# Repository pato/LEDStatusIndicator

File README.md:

LEDStatusIndicator
==================

Handy device that you can use to inform people outside your dorm on whether you are available, working, sleeping, or in need of solitude

First Protype
-------------
The first prototype was just a breadboard with four LEDs. There was no way of changing color besides manually using a jump cable to power them.

Second Protype
--------------
The second prototype did not use a breadboard, instead I soldered the cables to the resistors to the LEDs. The anodes are all soldered together and the cathod so the LEDs are toggled by manually providing power to the desired LED.

Third Prototype
---------------
The third prototype was housed in a cardboard box, the cables to power the LEDs would go over and around the door to the inside of the room where I could control which lights turn on.

Fourth Prototype
----------------
The fourth prototype uses an ATMega168, a push button, and an RGB LED. The button iterates through the various preset colors on the LED.

This is how it looks on the other side of the door.

Fifth Prototype
---------------
The goal of the fifth protype was to reduce parts, size, and costs, as well as make it battery powered. We used an ATTiny45, a capacitor, four resistors, a push button, jumper cables, and RGB LED.

In order to make it battery powered, we drastically reduced the frequence of the internal oscillator as well as made the LED pulse at interval instead of constnatly on.

First Beta
----------
The PCB boards from our friends at Oshpark! (PS: They're awesome!)

From the backside

From the front side

Here's how it looks mounted on the door!

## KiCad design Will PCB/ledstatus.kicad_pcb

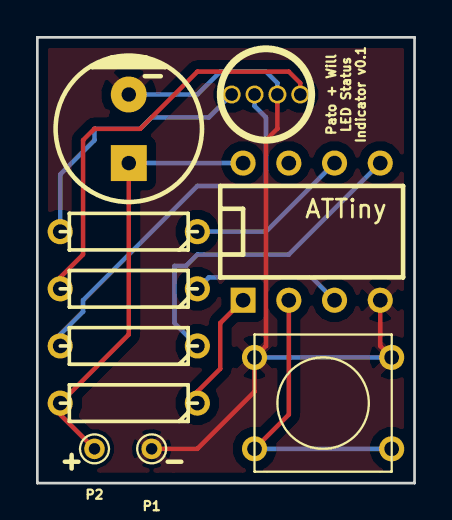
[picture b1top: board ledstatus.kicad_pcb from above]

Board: 2 copper layers, 21.0 x 24.8 mm, 10 parts (0 on the bottom side), 10 nets.

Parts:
C1: CP; CP_8x13mm
IC1: ATTINY25-P; DIP-8__300
LED1: LED_RCBG; LED5_RGB
P1, P2: CONN_1; PINTST
R1, R2, R3, R4: R; R3
SW1: SW_PUSH; SW_PUSH_SMALL

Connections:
GND: C1.2, IC1.4, LED1.2, P1.1, SW1.1
unnamed: IC1.2, SW1.2
unnamed: C1.1, IC1.8, P2.1, R4.2
unnamed: IC1.1, R4.1
unnamed: IC1.5, R3.1
unnamed: IC1.6, R2.1
unnamed: IC1.3, R1.1
unnamed: LED1.1, R1.2
unnamed: LED1.4, R2.2
unnamed: LED1.3, R3.2

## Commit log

2013-09-22 Adding first version of code
2013-09-22 Allows to compile and flash easily
2013-09-22 Added first board design
2013-09-23 Added pictures
2013-09-23 Added pictures to readme
2013-09-23 fixed image urls
2013-09-23 fixed images
2013-09-23 fixed image
2013-09-23 Added picture descriptions
2013-09-24 Removed unused code
2013-09-24 removed unused macros
2013-09-24 Added ignoring of elf and hex
2013-09-24 used watchdog timer
2013-09-25 Added parts list
2013-09-28 Did a bunch of LED stuff
2013-09-28 doing led stuff
2013-09-30 update added PCB
2013-09-30 added small version
2013-09-30 optimizing
2013-09-30 Messed with led programming
2013-09-30 Added Will's PCB
2013-10-01 using software pwm
2013-10-01 working software PWM and button interrupt
2013-10-01 pcb files
2013-10-01 Working software
2013-10-01 added fifth prototype
2013-10-01 initial upload
2013-10-01 Create gh-pages branch via GitHub
2013-10-03 Updated parts list --will
2013-10-05 editing LED stuff
2013-10-05 Cleaned up
2013-10-06 Super duper power efficient (4.5uA idle)
2013-10-08 added cases research
2013-10-20 final version
2013-10-20 added new pictures
2013-10-20 added picture files
2013-10-20 added beta pictures
2013-10-20 added other side of door
2013-10-22 Decreased power consumption and fixed debouncing
2013-11-01 New PCBs
2013-11-10 Software and UI improvements. Tested on hardware.
2013-12-29 Removed old PCBs again
2013-12-29 Changed PCB folder name
2013-12-29 Re-named a bunch of stuff
2013-12-29 Updated schematic
2013-12-29 Updated firmware for new PCB
2013-12-29 It's working!
2013-12-29 Added watchdog reset in pin change interrupt
2014-01-04 cleaned gerber files
2014-02-03 updated parts list
2014-02-03 updated parts
2014-02-03 Added rendered images of the top and bottom PCB layers
2014-02-14 Updated parts.txt with new reset resistor
2014-02-21 Updated for new hardware
    Also removed yellow color
2014-03-08 Added CAD PDF File
    Exactly what it says on the tin.
2014-03-08 made name url friendly
2014-03-23 Added the initial prototype 3D modeling files. I also included the .stl file for the case, incase it is needed.
2014-04-12 Fixed .stl units
2014-05-02 Added new separte part files and respective .stl files
2014-09-08 Added new Plate design (Front_Plate)
